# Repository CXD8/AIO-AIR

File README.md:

# AIO-AIR
 \
**Project Overview**\
This is a compact, custom air quality monitor built around the ESP32-S3. I designed it to be an all-in-one solution for tracking environmental data, giving me a much better understanding of the air quality in my workspace.\
## Disclaimer
- **This project is intended for educational and research purposes only**
- **The author accepts no liability for regulatory non-compliance resulting from use of this project**
- **Users are solely responsible for ensuring compliance with all applicable local laws and regulations**
This project is provided **as-is, with absolutely no warranty of any kind**, express or implied. The author(s) accept **zero responsibility or liability** for any outcome resulting from the use, assembly, or operation of this hardware - including but not limited to property damage, fire, personal injury, or death.

**Use entirely at your own risk. The author(s) have no responsibility whatsoever for anything that goes wrong.**
- **Regulatory Disclaimer**
This project may use uncertified radio frequency (RF) modules. These components may have not been independently tested or certified for compliance such as for FCC (USA), CE (EU), or any other regulatory framework.
ard.**. The author(s) accept no responsibility for any damage, injury, or death caused.
- **No certification.** This design has not been tested, certified, or approved for any commercial, consumer, safety-critical, or regulatory-controlled application.
- **No guarantees.** The author(s) make no guarantees regarding the accuracy or fitness for purpose of the schematic, BOM, firmware, or any associated documentation.
**By using, building, or operating this project in any form, you accept full and sole responsibility for all risks and any consequences that arise.**
By using this project in any form, you agree to assume all associated risks and responsibilities.

**How to Use**\
Flashing: No integrated usb flashing feature. You can use your choice of usb flashing device eg FT or CH chipsets, connect them respectively on the PCB via the headers. Copy firmware into Ardiuno IDE or preffered flashing software, then flash directly.\
Integration: The device is built to talk directly to Home Assistant via ESPHome/MQTT. Once you flash the firmware, it will show up as a sensor entity on your dashboard.\
Features: You can view real-time data on your dashboard or through the low power e ink display. Optional fan with control and speed, status etc. Flexible desing, connect any device to the respective power, uart or spi pins.\

**Why I Built This**\
Many makers do soldering, 3D printing, and working with various materials in an enclosed space.I designed this board to get accurate, reliable readings so I can actually manage the air quality while I work. Also for monitoring Co2 because sleep is important :) |
 \

Bill Of Materials
| **#** | **bom\.csv**                                             | ****  | ****  | ****        | ****                                         | ****  | ****                 | ****     | ****                | ****                              | ****                               | ****                       | ****        | ****              | ****                      | ****      | ****                                   | **** | **** | **** | ****         | ****          | ****           | ****                                                                                                                                                                        | ****           | ****                                                   |
|-------|----------------------------------------------------------|-------|-------|-------------|----------------------------------------------|-------|----------------------|----------|---------------------|-----------------------------------|------------------------------------|----------------------------|-------------|-------------------|---------------------------|-----------|----------------------------------------|------|------|------|--------------|---------------|----------------|-----------------------------------------------------------------------------------------------------------------------------------------------------------------------------|----------------|--------------------------------------------------------|
| 1     |                                                          |       |       |             |                                              |       |                      |          |                     |                                   | BOM Date Created:23/05/26          |                            |             |                   | BOM Export Date: 23/05/26 |           |                                        |      |      |      |              |               |                |                                                                                                                                                                             |                |                                                        |
| 2     |                                                          |       |       |             |                                              |       |                      |          |                     |                                   | EST LCSC TOTAL: $30\.73           |                            |             |                   |                           |           |                                        |      |      |      |              |               |                |                                                                                                                                                                             |                |                                                        |
| 3     |                                                       |       |       |             |                                              |       |                      |          |                     |                                   | TOTAL – 1 SEN55 Sensor: $92\.61           |                            |             |                   |                           |           |                                        |      |      |      |              |               |                |                                                                                                                                                                             |                |                                                        |
| 4     | Uploaded data                                            |       |       |             |                                              |       |                      |          |                     |                                   | LCSC Matching Results              |                            |             |                   |                           |           |                                        |      |      |      |              |               |                |                                                                                                                                                                             |                |                                                        |
| 5     | LCSC\#                                                   | Mfr\. | Mrf\# | Description | Package                                      | Value | Customer Part Number | Quantity | Target Price\(USD\) | Target Lead Time\(Business Days\) | Mrf\#                              | Mfr\.                      | Order Qty\. | Unit Price\(USD\) | Ext\.Price\(USD\)         | LCSC\#    | Package                                | Min  | Mult | SPQ  | Availability | Stock Status  | Customer Notes | Description                                                                                                                                                                 | Matched status | Product Link                                           |
| 6     | C15849                                                   |       |       |             | C0603                                        |       | \-                   | 11       |                     |                                   | CL10A105KB8NNNC                    | Samsung Electro\-Mechanics | 50          | 0\.0077           | 0\.39                     | C15849    | 0603                                   | 50   | 50   | 4000 | 4032550      | In Stock      |                | 1uF ±10% 50V Ceramic Capacitor X5R 0603                                                                                                                                     | Exact Matches  | https://www\.lcsc\.com/product\-detail/C15849\.html    |
| 7     | C96446                                                   |       |       |             | C0603                                        |       | \-                   | 10       |                     |                                   | CL10A106MA8NRNC                    | Samsung Electro\-Mechanics | 20          | 0\.0223           | 0\.45                     | C96446    | 0603                                   | 20   | 20   | 4000 | 277300       | In Stock      |                | 10uF ±20% 25V Ceramic Capacitor X5R 0603                                                                                                                                    | Exact Matches  | https://www\.lcsc\.com/product\-detail/C96446\.html    |
| 8     | C1591                                                    |       |       |             | C0603                                        |       | \-                   | 10       |                     |                                   | CL10B104KB8NNNC                    | Samsung Electro\-Mechanics | 100         | 0\.0032           | 0\.32                     | C1591     | 0603                                   | 100  | 100  | 4000 | 1456500      | In Stock      |                | 100nF ±10% 50V Ceramic Capacitor X7R 0603                                                                                                                                   | Exact Matches  | https://www\.lcsc\.com/product\-detail/C1591\.html     |
| 9     | C307467                                                  |       |       |             | C0603                                        |       | \-                   | 4        |                     |                                   | CL10A475KL8NRNC                    | Samsung Electro\-Mechanics | 5           | 0\.0304           | 0\.15                     | C307467   | 0603                                   | 5    | 5    | 4000 | 192075       | In Stock      |                | 4\.7uF ±10% 35V Ceramic Capacitor X5R 0603                                                                                                                                  | Exact Matches  | https://www\.lcsc\.com/product\-detail/C307467\.html   |
| 10    | C883598                                                  |       |       |             | C1206                                        |       | \-                   | 4        |                     |                                   | GRM31CR61A107MEA8L                 | muRata                     | 5           | 0\.1955           | 0\.98                     | C883598   | 1206                                   | 5    | 5    | 2000 | 209960       | In Stock      |                | 100uF ±20% 10V Ceramic Capacitor X5R 1206                                                                                                                                   | Exact Matches  | https://www\.lcsc\.com/product\-detail/C883598\.html   |
| 11    | C21122                                                   |       |       |             | C0603                                        |       | \-                   | 3        |                     |                                   | CL10B223KB8NNNC                    | Samsung Electro\-Mechanics | 50          | 0\.0046           | 0\.23                     | C21122    | 0603                                   | 50   | 50   | 4000 | 1335100      | In Stock      |                | 22nF ±10% 50V Ceramic Capacitor X7R 0603                                                                                                                                    | Exact Matches  | https://www\.lcsc\.com/product\-detail/C21122\.html    |
| 12    | C307467                                                  |       |       |             | C0603                                        |       | \-                   | 3        |                     |                                   | CL10A475KL8NRNC                    | Samsung Electro\-Mechanics | 5           | 0\.0304           | 0\.15                     | C307467   | 0603                                   | 5    | 5    | 4000 | 192075       | In Stock      |                | 4\.7uF ±10% 35V Ceramic Capacitor X5R 0603                                                                                                                                  | Exact Matches  | https://www\.lcsc\.com/product\-detail/C307467\.html   |
| 13    | C6119851                                                 |       |       |             | C0603                                        |       | \-                   | 2        |                     |                                   | CGA0603X5R475K350JT                | HRE                        | 20          | 0\.0304           | 0\.61                     | C6119851  | 0603                                   | 20   | 20   | 4000 | 18100        | In Stock      |                | 4\.7uF ±10% 35V Ceramic Capacitor X5R 0603                                                                                                                                  | Exact Matches  | https://www\.lcsc\.com/product\-detail/C6119851\.html  |
| 14    | C1591                                                    |       |       |             | C0603                                        |       | \-                   | 2        |                     |                                   | CL10B104KB8NNNC                    | Samsung Electro\-Mechanics | 100         | 0\.0032           | 0\.32                     | C1591     | 0603                                   | 100  | 100  | 4000 | 1456500      | In Stock      |                | 100nF ±10% 50V Ceramic Capacitor X7R 0603                                                                                                                                   | Exact Matches  | https://www\.lcsc\.com/product\-detail/C1591\.html     |
| 15    | C6563232                                                 |       |       |             | C0603                                        |       | \-                   | 1        |                     |                                   | 0603B112K500NT                     | FH                         | 100         | 0\.0030           | 0\.30                     | C6563232  | 0603                                   | 100  | 100  | 4000 | 400          | In Stock      |                | 1\.1nF ±10% 50V Ceramic Capacitor X7R 0603                                                                                                                                  | Exact Matches  | https://www\.lcsc\.com/product\-detail/C6563232\.html  |
| 16    | C1591                                                    |       |       |             | C0603                                        |       | \-                   | 1        |                     |                                   | CL10B104KB8NNNC                    | Samsung Electro\-Mechanics | 100         | 0\.0032           | 0\.32                     | C1591     | 0603                                   | 100  | 100  | 4000 | 1456500      | In Stock      |                | 100nF ±10% 50V Ceramic Capacitor X7R 0603                                                                                                                                   | Exact Matches  | https://www\.lcsc\.com/product\-detail/C1591\.html     |
| 17    | C86295                                                   |       |       |             | C0603                                        |       | \-                   | 1        |                     |                                   | CL10A226MP8NUNE                    | Samsung Electro\-Mechanics | 10          | 0\.0157           | 0\.16                     | C86295    | 0603                                   | 10   | 10   | 3000 | 1989760      | In Stock      |                | 22uF ±20% 10V Ceramic Capacitor X5R 0603                                                                                                                                    | Exact Matches  | https://www\.lcsc\.com/product\-detail/C86295\.html    |
| 18    | C98220                                                   |       |       |             | R0603                                        |       | \-                   | 5        |                     |                                   | RC0603FR\-0710KL                   | YAGEO                      | 100         | 0\.0015           | 0\.15                     | C98220    | 0603                                   | 100  | 100  | 5000 | 0            | Backordered   |                | 100mW 10k? 75V Thick Film Resistor ±100ppm/? ±1% 0603 Chip Resistor \- Surface Mount RoHS                                                                                   | Exact Matches  | https://www\.lcsc\.com/product\-detail/C98220\.html    |
| 19    | C14675                                                   |       |       |             | R0603                                        |       | \-                   | 5        |                     |                                   | RC0603FR\-07100KL                  | YAGEO                      | 100         | 0\.0014           | 0\.14                     | C14675    | 0603                                   | 100  | 100  | 5000 | 1073900      | In Stock      |                | 100mW 100k? 75V Thick Film Resistor ±100ppm/? ±1% 0603 Chip Resistor \- Surface Mount RoHS                                                                                  | Exact Matches  | https://www\.lcsc\.com/product\-detail/C14675\.html    |
| 20    | C25804                                                   |       |       |             | R0603                                        |       | \-                   | 4        |                     |                                   | 0603WAF1002T5E                     | UNI\-ROYAL                 | 100         | 0\.0014           | 0\.14                     | C25804    | 0603                                   | 100  | 100  | 5000 | 0            | Backordered   |                | 10k? ±1% 100mW 0603 Thick Film Resistor                                                                                                                                     | Exact Matches  | https://www\.lcsc\.com/product\-detail/C25804\.html    |
| 21    | C95177                                                   |       |       |             | R0603                                        |       | \-                   | 4        |                     |                                   | RC0603JR\-070RL                    | YAGEO                      | 100         | 0\.0014           | 0\.14                     | C95177    | 0603                                   | 100  | 100  | 5000 | 1026800      | In Stock      |                | 100mW 0? 75V Thick Film Resistor ±5% 0603 Chip Resistor \- Surface Mount RoHS                                                                                               | Exact Matches  | https://www\.lcsc\.com/product\-detail/C95177\.html    |
| 22    | C25804                                                   |       |       |             | R0603                                        |       | \-                   | 2        |                     |                                   | 0603WAF1002T5E                     | UNI\-ROYAL                 | 100         | 0\.0014           | 0\.14                     | C25804    | 0603                                   | 100  | 100  | 5000 | 0            | Backordered   |                | 10k? ±1% 100mW 0603 Thick Film Resistor                                                                                                                                     | Exact Matches  | https://www\.lcsc\.com/product\-detail/C25804\.html    |
| 23    | C114659                                                  |       |       |             | R0603                                        |       | \-                   | 2        |                     |                                   | RC0603FR\-0712KL                   | YAGEO                      | 100         | 0\.0016           | 0\.16                     | C114659   | 0603                                   | 100  | 100  | 5000 | 1073600      | In Stock      |                | 12k? 100mW 75V Thick Film Resistor ±100ppm/? ±1% 0603 Chip Resistor \- Surface Mount RoHS                                                                                   | Exact Matches  | https://www\.lcsc\.com/product\-detail/C114659\.html   |
| 24    | C52069115                                                |       |       |             | R0603                                        |       | \-                   | 1        |                     |                                   | MFCR0603F3R00Q9R                   | RESI                       | 5           | 0\.0840           | 0\.42                     | C52069115 | 0603                                   | 5    | 5    | 5000 | 4610         | In Stock      |                | 3? 400mW ±50ppm/? ±1% 0603 Chip Resistor \- Surface Mount RoHS                                                                                                              | Exact Matches  | https://www\.lcsc\.com/product\-detail/C52069115\.html |
| 25    | C23411                                                   |       |       |             | R0603                                        |       | \-                   | 1        |                     |                                   | 0603WAF470LT5E                     | UNI\-ROYAL                 | 100         | 0\.0051           | 0\.51                     | C23411    | 0603                                   | 100  | 100  | 5000 | 59400        | In Stock      |                | 470m? ±1% 100mW 0603 Thick Film Resistor                                                                                                                                    | Exact Matches  | https://www\.lcsc\.com/product\-detail/C23411\.html    |
| 26    | C22883                                                   |       |       |             | R0603                                        |       | \-                   | 1        |                     |                                   | 0603WAF1583T5E                     | UNI\-ROYAL                 | 100         | 0\.0014           | 0\.14                     | C22883    | 0603                                   | 100  | 100  | 5000 | 166400       | In Stock      |                | 158k? ±1% 100mW 0603 Thick Film Resistor                                                                                                                                    | Exact Matches  | https://www\.lcsc\.com/product\-detail/C22883\.html    |
| 27    | C107231                                                  |       |       |             | R0603                                        |       | \-                   | 1        |                     |                                   | RC0603FR\-0751KL                   | YAGEO                      | 100         | 0\.0016           | 0\.16                     | C107231   | 0603                                   | 100  | 100  | 5000 | 140700       | In Stock      |                | 100mW 51k? 75V Thick Film Resistor ±100ppm/? ±1% 0603 Chip Resistor \- Surface Mount RoHS                                                                                   | Exact Matches  | https://www\.lcsc\.com/product\-detail/C107231\.html   |
| 28    | C22892                                                   |       |       |             | R0603                                        |       | \-                   | 1        |                     |                                   | 0603WAF1822T5E                     | UNI\-ROYAL                 | 100         | 0\.0012           | 0\.12                     | C22892    | 0603                                   | 100  | 100  | 5000 | 17100        | In Stock      |                | 18\.2k? ±1% 100mW 0603 Thick Film Resistor                                                                                                                                  | Exact Matches  | https://www\.lcsc\.com/product\-detail/C22892\.html    |
| 29    | C105574                                                  |       |       |             | R0603                                        |       | \-                   | 1        |                     |                                   | RC0603FR\-07200KL                  | YAGEO                      | 100         | 0\.0016           | 0\.16                     | C105574   | 0603                                   | 100  | 100  | 5000 | 196200       | In Stock      |                | 100mW 200k? 75V Thick Film Resistor ±100ppm/? ±1% 0603 Chip Resistor \- Surface Mount RoHS                                                                                  | Exact Matches  | https://www\.lcsc\.com/product\-detail/C105574\.html   |
| 30    | C2930091                                                 |       |       |             | R0603                                        |       | \-                   | 1        |                     |                                   | FRC0603F3003TS                     | FOJAN                      | 100         | 0\.0011           | 0\.11                     | C2930091  | 0603                                   | 100  | 100  | 5000 | 1794600      | In Stock      |                | 300k? ±1% 100mW 0603 Thick Film Resistor                                                                                                                                    | Exact Matches  | https://www\.lcsc\.com/product\-detail/C2930091\.html  |
| 31    | C105579                                                  |       |       |             | R0603                                        |       | \-                   | 1        |                     |                                   | RC0603FR\-0747KL                   | YAGEO                      | 100         | 0\.0016           | 0\.16                     | C105579   | 0603                                   | 100  | 100  | 5000 | 370600       | In Stock      |                | 100mW 47k? 75V Thick Film Resistor ±100ppm/? ±1% 0603 Chip Resistor \- Surface Mount RoHS                                                                                   | Exact Matches  | https://www\.lcsc\.com/product\-detail/C105579\.html   |
| 32    | C2998085                                                 |       |       |             | R0603                                        |       | \-                   | 1        |                     |                                   | FRC0603F9001TS                     | FOJAN                      | 0           | \-                | \-                        | C2998085  | 0603                                   | 100  | 100  | 5000 | 0            | discountinued |                | 9k? ±1% 100mW 0603 Thick Film Resistor                                                                                                                                      | Exact Matches  | https://www\.lcsc\.com/product\-detail/C2998085\.html  |
| 33    | C109318                                                  |       |       |             | R0603                                        |       | \-                   | 1        |                     |                                   | RC0603FR\-0710RL                   | YAGEO                      | 100         | 0\.0039           | 0\.39                     | C109318   | 0603                                   | 100  | 100  | 5000 | 3822900      | In Stock      |                | 100mW 10? 75V Thick Film Resistor ±1% ±200ppm/? 0603 Chip Resistor \- Surface Mount RoHS                                                                                    | Exact Matches  | https://www\.lcsc\.com/product\-detail/C109318\.html   |
| 34    | C22461457                                                |       |       |             | RES\-ADJ\-SMD\_3P\-L3\.8\-W3\.7\_VGF39NCHXT  |       | \-                   | 1        |                     |                                   | VGF39NCHXT\-B201                   | HDK                        | 5           | 0\.1107           | 0\.55                     | C22461457 | SMD\-3P,3\.8x3\.7mm                    | 5    | 5    | 2500 | 2525         | In Stock      |                | 200? ±25% 150mW SMD Potentiometers, Variable Resistors                                                                                                                      | Exact Matches  | https://www\.lcsc\.com/product\-detail/C22461457\.html |
| 35    | C105881                                                  |       |       |             | R0603                                        |       | \-                   | 1        |                     |                                   | RC0603FR\-07330RL                  | YAGEO                      | 100         | 0\.0015           | 0\.15                     | C105881   | 0603                                   | 100  | 100  | 5000 | 351200       | In Stock      |                | 100mW 330? 75V Thick Film Resistor ±100ppm/? ±1% 0603 Chip Resistor \- Surface Mount RoHS                                                                                   | Exact Matches  | https://www\.lcsc\.com/product\-detail/C105881\.html   |
| 36    | C2875591                                                 |       |       |             | IND\-SMD\_L4\.7\-W4\.7                       |       | \-                   | 2        |                     |                                   | CDH4D28N\-100M                     | MINGSTAR                   | 5           | 0\.1803           | 0\.90                     | C2875591  | SMD,4\.7x4\.7mm                        | 5    | 5    | 2500 | 2505         | In Stock      |                | 1A 10uH ±20% 128\.3m? SMD,4\.7x4\.7mm Fixed Inductors RoHS                                                                                                                  | Exact Matches  | https://www\.lcsc\.com/product\-detail/C2875591\.html  |
| 37    | C436534                                                  |       |       |             | IND\-SMD\_L5\.4\-W5\.2\_PSPMAA0503           |       | \-                   | 1        |                     |                                   | PSPMAA0503\-3R3M\-ANP              | PROD Tech                  | 5           | 0\.1292           | 0\.65                     | C436534   | SMD,5\.4x5\.2mm                        | 5    | 5    | 2000 | 4805         | In Stock      |                | 5A 3\.3uH ±20% 6A 38m? SMD,5\.4x5\.2mm Fixed Inductors RoHS                                                                                                                 | Exact Matches  | https://www\.lcsc\.com/product\-detail/C436534\.html   |
| 38    | C7436545                                                 |       |       |             | SOD\-123\_L2\.8\-W1\.8\-LS3\.9\-FD           |       | \-                   | 4        |                     |                                   | MBR0530T1G                         | FUXINSEMI                  | 10          | 0\.0162           | 0\.16                     | C7436545  | SOD\-123                               | 10   | 10   | 3000 | 5700         | In Stock      |                | Diode Independent 30V 0\.5A Surface Mount SOD\-123                                                                                                                          | Exact Matches  | https://www\.lcsc\.com/product\-detail/C7436545\.html  |
| 39    | C110921                                                  |       |       |             | SOD\-123F\_L2\.8\-W1\.8\-LS3\.7\-RD          |       | \-                   | 1        |                     |                                   | PMEG2010AEH,115                    | Nexperia                   | 5           | 0\.2158           | 1\.08                     | C110921   | SOD\-123F                              | 5    | 5    | 3000 | 5360         | In Stock      |                | Diode 1 Independent 20V 1A Surface Mount SOD\-123F                                                                                                                          | Exact Matches  | https://www\.lcsc\.com/product\-detail/C110921\.html   |
| 40    | C150716                                                  |       |       |             | SOT\-223\_L6\.7\-W3\.5\-P2\.30\-BR           |       | \-                   | 3        |                     |                                   | AP2114H\-3\.3TRG1                  | DIODES                     | 5           | 0\.1763           | 0\.88                     | C150716   | SOT\-223                               | 5    | 5    | 4000 | 14765        | In Stock      |                | 3\.3V Positive Fixed SOT\-223 Voltage Regulators \- Linear, Low Drop Out \(LDO\) Regulators RoHS                                                                            | Exact Matches  | https://www\.lcsc\.com/product\-detail/C150716\.html   |
| 41    | C15651                                                   |       |       |             | SOT\-23\-5\_L3\.0\-W1\.7\-P0\.95\-LS2\.8\-BL |       | \-                   | 3        |                     |                                   | RT9193\-33GB                       | RICHTEK                    | 5           | 0\.1271           | 0\.64                     | C15651    | SOT\-23\-5                             | 5    | 5    | 3000 | 0            | Backordered   |                | 3\.3V Positive Fixed SOT\-23\-5 Voltage Regulators \- Linear, Low Drop Out \(LDO\) Regulators RoHS                                                                          | Exact Matches  | https://www\.lcsc\.com/product\-detail/C15651\.html    |
| 42    | C3013946                                                 |       |       |             | WIRELM\-SMD\_ESP32\-S3\-WROOM\-1U            |       | \-                   | 1        |                     |                                   | ESP32\-S3\-WROOM\-1U\-N16R8        | ESPRESSIF                  | 1           | 5\.5217           | 5\.52                     | C3013946  | SMD,19\.2x18mm                         | 1    | 1    | 650  | 0            | Backordered   |                | 2\.4GHz ESP32\-S3R8 \-103\.5dBm SMD,19\.2x18mm RF Transceiver Modules and Modems RoHS                                                                                       | Exact Matches  | https://www\.lcsc\.com/product\-detail/C3013946\.html  |
| 43    | C113659                                                  |       |       |             | VSSOP\-8\_L3\.0\-W3\.0\-P0\.65\-LS5\.0\-BL   |       | \-                   | 1        |                     |                                   | TPS61085DGKR                       | TI                         | 1           | 0\.5915           | 0\.59                     | C113659   | VSSOP\-8\-0\.65mm                      | 1    | 1    | 2500 | 4530         | In Stock      |                | Boost Adjustable 2\.8V~18\.5V 2A 2\.3V~6V VSSOP\-8\-0\.65mm Voltage Regulators \- DC DC Switching Regulators RoHS                                                           | Exact Matches  | https://www\.lcsc\.com/product\-detail/C113659\.html   |
| 44    | C664389                                                  |       |       |             | SOT\-23\-5\_L3\.0\-W1\.6\-P0\.95\-LS2\.8\-BL |       | \-                   | 1        |                     |                                   | LT1615IS5\#TRPBF                   | ADI                        | 1           | 6\.0924           | 6\.09                     | C664389   | TSOT\-23\-5                            | 1    | 1    | 2500 | 143          | In Stock      |                | Boost Adjustable 1V~15V 1\.23V~34V 300mA TSOT\-23\-5 Voltage Regulators \- DC DC Switching Regulators RoHS                                                                  | Exact Matches  | https://www\.lcsc\.com/product\-detail/C664389\.html   |
| 45    | C3293144                                                 |       |       |             | SW\-SMD\_8P\-L6\.7\-W5\.4\-P1\.27\-LS8\.4    |       | \-                   | 1        |                     |                                   | DSHP04TSGER                        | kangshen                   | 4           | 0\.5202           | 2\.08                     | C3293144  | SMD,P=1\.27mm                          | 4    | 4    | 2000 | 29172        | In Stock      |                | Dip Switch SPST 4 Position Surface Mount\-8P,5\.4x6\.6mm 25mA 24V                                                                                                           | Exact Matches  | https://www\.lcsc\.com/product\-detail/C3293144\.html  |
| 46    | C963206                                                  |       |       |             | SW\-SMD\_MK\-12C02\-G020                     |       | \-                   | 2        |                     |                                   | MK\-12C02\-G020                    | G\-Switch                  | 5           | 0\.1168           | 0\.58                     | C963206   | SMD,6\.6x1\.4mm                        | 5    | 5    | 3000 | 9555         | In Stock      |                | Slide Switch SPDT 1A @ 6V Surface Mount, Right Angle Rectangular Columnar 6\.6mm                                                                                            | Exact Matches  | https://www\.lcsc\.com/product\-detail/C963206\.html   |
| 47    | C720477                                                  |       |       |             | SW\-SMD\_L3\.9\-W3\.0\-P4\.45                |       | \-                   | 2        |                     |                                   | TS\-1088\-AR02016                  | XUNPU                      | 10          | 0\.0538           | 0\.54                     | C720477   | SMD,4x3mm                              | 10   | 10   | 4000 | 582850       | In Stock      |                | Tactile Switch SPST 160gf 2mm SMD \(SMT\) Tab 4mm x 3mm Surface Mount                                                                                                       | Exact Matches  | https://www\.lcsc\.com/product\-detail/C720477\.html   |
| 48    | C2856796                                                 |       |       |             | FPC\-SMD\_6P\-P0\.50\_XUNPU\_FPC\-05F\-6PH20 |       | \-                   | 3        |                     |                                   | FPC\-05F\-6PH20                    | XUNPU                      | 5           | 0\.1000           | 0\.50                     | C2856796  | SMD,P=0\.5mm,Surface Mount,Right Angle | 5    | 5    | 2000 | 66135        | In Stock      |                | FFC/FPC Connector 6 Position 0\.5mm Pitch Bottom Contact Surface Mount, Right Angle \-25?~\+85?                                                                             | Exact Matches  | https://www\.lcsc\.com/product\-detail/C2856796\.html  |
| 49    | C240840                                                  |       |       |             | 4PIN\_FAN\_PWM                               |       | \-                   | 1        |                     |                                   | 470531000                          | MOLEX                      | 5           | 0\.1803           | 0\.90                     | C240840   | Through Hole,P=2\.54mm                 | 5    | 5    | 1000 | 21670        | In Stock      |                | Connector Header 4 position 2\.54mm Pitch Through Hole                                                                                                                      | Exact Matches  | https://www\.lcsc\.com/product\-detail/C240840\.html   |
| 50    |                                                          |       |       |             | FLASH                                        |       | \-                   | 1        |                     |                                   | \-                                 | \-                         | \-          | \-                | \-                        | \-        | \-                                     | \-   | \-   | \-   | \-           | \-            |                | \-                                                                                                                                                                          | \-             |                                                        |
| 51    | C3446015                                                 |       |       |             | FPC\-SMD\_XUNPU\-FPC\-0\.5FX\-24PWBH20       |       | \-                   | 1        |                     |                                   | FPC\-0\.5FX\-24PWBH20              | XUNPU                      | 5           | 0\.1424           | 0\.71                     | C3446015  | SMD,P=0\.5mm                           | 5    | 5    | 2000 | 3065         | In Stock      |                | Hinged Lid \-25?~\+85? 24P 0\.5mm 500mA 50V Tin Bottom Contact Surface Mount, Right Angle Phosphor bronze SMD,P=0\.5mm FFC, FPC \(Flat Flexible\) Connector Assemblies RoHS | Exact Matches  | https://www\.lcsc\.com/product\-detail/C3446015\.html  |
| 52    | C219228                                                  |       |       |             | LED\-SMD\_L1\.6\-W0\.8\-RD\-WHITE\-2         |       | \-                   | 1        |                     |                                   | HL\-PST\-1608H233W\(8000\-12000K\) | HONGLITRONIC               | 20          | 0\.0197           | 0\.39                     | C219228   | 0603                                   | 20   | 20   | 4000 | 73360        | In Stock      |                | White LED Indication \- Discrete 3\.3V 0603                                                                                                                                 | Exact Matches  | https://www\.lcsc\.com/product\-detail/C219228\.html   |
| 53    | https://www\.aliexpress\.com/item/1005009258276115\.html |       |       |             | 4\.2”E\-INK                                  |       | \-                   | 1        |                     |                                   | GDEY042T81\-T02                    | GooDisplay                 | 1           | 22\.46            | 22\.46                    | \-        | \-                                     | \-   | \-   | \-   | \-           | \-            |                | \-                                                                                                                                                                          | ALIEXPRESS     |                                                        |
| 54    | C3289597                                                 |       |       |             | SOT\-323\_L2\.0\-W1\.3\-P1\.30\-LS2\.1\-BR   |       | \-                   | 1        |                     |                                   | SI1308EDL\-T1\-BE3                 | VISHAY                     | 1           | 0\.4041           | 0\.40                     | C3289597  | SC\-70\-3                              | 1    | 1    | 3000 | 2243         | In Stock      |                | N\-Channel 30V 1\.5A 0\.5W Surface Mount SC\-70\-3                                                                                                                          | Exact Matches  | https://www\.lcsc\.com/product\-detail/C3289597\.html  |
| 55    | https://www\.aliexpress\.com/item/1005008474655738\.html |       |       |             | 24 PIN FPC CABLE                             |       | \-                   | 1        |                     |                                   | \-                                 | \-                         | \-          | 0\.99             | 0\.99                     | \-        | \-                                     | \-   | \-   | \-   | \-           | \-            |                | \-                                                                                                                                                                          | ALIEXPRESS     |                                                        |
| 56    | https://www\.aliexpress\.com/item/1005006672233038\.html |       | \-    |             | SEN55                                        | \-    | \-                   | 1        | \-                  | \-                                | SEN55                              | Sensirion                  |             | 38\.43            | 38\.43                    | \-        | \-                                     | \-   | \-   | \-   | \-           | \-            |                | \-                                                                                                                                                                          | ALIEXPRESS     |                                                        |

Changelog\
06/30/2026
New Housing/Case. Improved viewing angles, fits larger sensors, looks much better.
03/31/2026
Optimise PCB size under 100mmx100mm for cheaper fabrication costs.

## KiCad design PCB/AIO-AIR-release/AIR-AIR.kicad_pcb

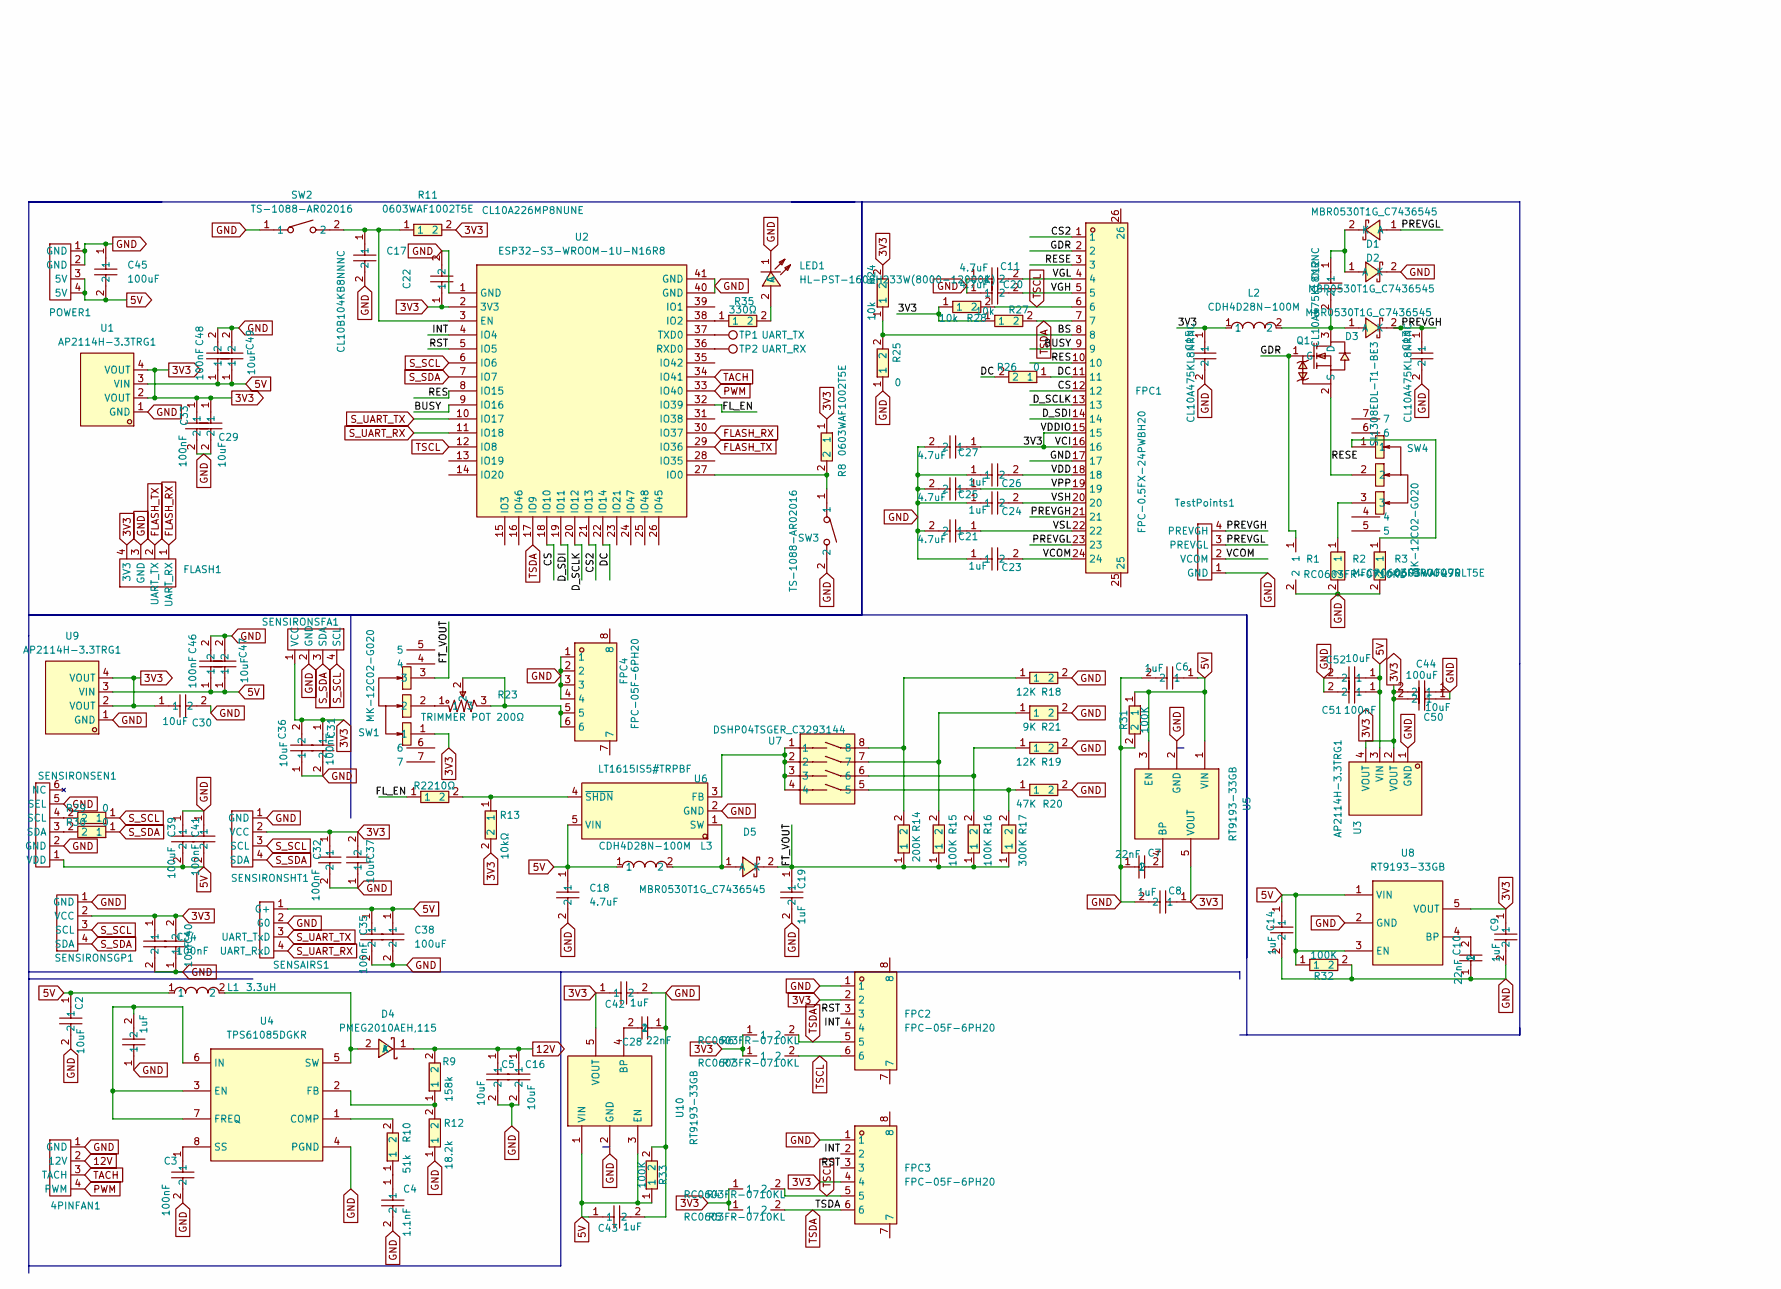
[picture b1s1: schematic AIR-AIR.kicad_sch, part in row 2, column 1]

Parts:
4PINFAN1: 4PIN_FAN_PWM
C1, C6, C8, C9, C14, C19, C23, C24, C26, C42, C43: 1uF; C0603; LCSC Part C15849
C2, C5, C16, C30, C36, C37, C40, C47, C49, C52: 10uF; C0603; LCSC Part C96446
C3, C31, C32, C33, C34, C35, C41, C46, C48, C51: 100nF; C0603; LCSC Part C1591
C4: 1.1nF; C0603; LCSC Part C6563232
C7, C10, C28: 22nF; C0603; LCSC Part C21122
C11, C20: 4.7uF; C0603; LCSC Part C6119851
C12, C13, C15: CL10A475KL8NRNC; C0603; LCSC Part C307467
C17: CL10B104KB8NNNC; C0603; LCSC Part C1591
C18, C21, C25, C27: 4.7uF; C0603; LCSC Part C307467
C22: CL10A226MP8NUNE; C0603; LCSC Part C86295
C29, C50: 10uF; C0603; LCSC Part C1591
C38, C39, C44, C45: 100uF; C1206; LCSC Part C883598
D1, D2, D3, D5: MBR0530T1G_C7436545; SOD-123_L2.8-W1.8-LS3.9-FD; LCSC Part C7436545
D4: PMEG2010AEH,115; SOD-123F_L2.8-W1.8-LS3.7-RD; LCSC Part C110921
FLASH1: FLASH
FPC1: FPC-0.5FX-24PWBH20; FPC-SMD_XUNPU-FPC-0.5FX-24PWBH20; LCSC Part C3446015
FPC2, FPC3, FPC4: FPC-05F-6PH20; FPC-SMD_6P-P0.50_XUNPU_FPC-05F-6PH20; LCSC Part C2856796
L1: 3.3uH; IND-SMD_L5.4-W5.2_PSPMAA0503; LCSC Part C436534
L2, L3: CDH4D28N-100M; IND-SMD_L4.7-W4.7; LCSC Part C2875591
LED1: HL-PST-1608H233W(8000-12000K); LED-SMD_L1.6-W0.8-RD-WHITE-2; LCSC Part C219228
POWER1: POWER
Q1: SI1308EDL-T1-BE3; SOT-323_L2.0-W1.3-P1.30-LS2.1-BR; LCSC Part C3289597
R1, R4, R5, R6, R7: RC0603FR-0710KL; R0603; LCSC Part C98220
R2: MFCR0603F3R00Q9R; R0603; LCSC Part C52069115
R3: 0603WAF470LT5E; R0603; LCSC Part C23411
R8, R11: 0603WAF1002T5E; R0603; LCSC Part C25804
R9: 158k; R0603; LCSC Part C22883
R10: 51k; R0603; LCSC Part C107231
R12: 18.2k; R0603; LCSC Part C22892
R13: 10kΩ; R0603; LCSC Part C25804
R14: 200K; R0603; LCSC Part C105574
R15, R16, R31, R32, R33: 100K; R0603; LCSC Part C14675
R17: 300K; R0603; LCSC Part C2930091
R18, R19: 12K; R0603; LCSC Part C114659
R20: 47K; R0603; LCSC Part C105579
R21: 9K; R0603; LCSC Part C2998085
R22: 10Ω; R0603; LCSC Part C109318
R23: TRIMMER POT 200Ω; RES-ADJ-SMD_3P-L3.8-W3.7_VGF39NCHXT; LCSC Part C22461457
R24, R27, R28: 10k; R0603; LCSC Part C25804
R25, R26, R29, R30: 0; R0603; LCSC Part C95177
R35: 330Ω; R0603; LCSC Part C105881
SENSAIRS1: SENSAIR_S88
SENSIRONSEN1: SENSIRON_SEN55
SENSIRONSFA1: SENSIRON_SFA40
SENSIRONSGP1: SENSIRON_SGP41
SENSIRONSHT1: SENSIRON_SHT45
SW1, SW4: MK-12C02-G020; SW-SMD_MK-12C02-G020; LCSC Part C963206
SW2, SW3: TS-1088-AR02016; SW-SMD_L3.9-W3.0-P4.45; LCSC Part C720477
TP1: UART_TX
TP2: UART_RX
TestPoints1: TestPoints
U1, U3, U9: AP2114H-3.3TRG1; SOT-223_L6.7-W3.5-P2.30-BR; LCSC Part C150716
U2: ESP32-S3-WROOM-1U-N16R8; WIRELM-SMD_ESP32-S3-WROOM-1U; LCSC Part C3013946
U4: TPS61085DGKR; VSSOP-8_L3.0-W3.0-P0.65-LS5.0-BL; LCSC Part C113659
U5, U8, U10: RT9193-33GB; SOT-23-5_L3.0-W1.7-P0.95-LS2.8-BL; LCSC Part C15651
U6: LT1615IS5#TRPBF; SOT-23-5_L3.0-W1.6-P0.95-LS2.8-BL; LCSC Part C664389
U7: DSHP04TSGER_C3293144; SW-SMD_8P-L6.7-W5.4-P1.27-LS8.4; LCSC Part C3293144

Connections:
3V3: C8.1, C9.1, C15.1, C22.1, C27.1, C29.1, C30.1, C31.1, C32.1, C33.1, C34.1, C36.2, C37.2, C40.2, C42.1, C44.2, C50.2, FLASH1.4 (3V3), FPC1.15, FPC1.16, FPC2.2, FPC3.4, L2.1, R4.1, R5.1, R6.1, R7.1, R8.1, R11.2, R13.2, R24.2, R27.1, R28.1, SENSIRONSFA1.1 (VCC), SENSIRONSGP1.2 (VCC), SENSIRONSHT1.2 (VCC), SW1.1, U1.2 (VOUT), U1.4 (VOUT), U2.2 (3V3), U3.2 (VOUT), U3.4 (VOUT), U5.5 (VOUT), U8.5 (VOUT), U9.2 (VOUT), U9.4 (VOUT), U10.5 (VOUT)
5V: C2.1, C6.1, C14.1, C18.1, C35.1, C38.1, C39.2, C41.2, C43.1, C45.2, C46.1, C47.1, C48.1, C49.1, C51.1, C52.1, L1.1, L3.1, POWER1.3 (5V), POWER1.4 (5V), R31.1, R32.1, R33.1, SENSAIRS1.1 (G+), SENSIRONSEN1.1 (VDD), U1.3 (VIN), U3.3 (VIN), U5.1 (VIN), U5.3 (EN), U6.5 (VIN), U8.1 (VIN), U8.3 (EN), U9.3 (VIN), U10.1 (VIN), U10.3 (EN)
12V: 4PINFAN1.2 (12V), C5.1, C16.1, D4.1 (K), R9.2
/BS: FPC1.8, R24.1, R25.2
/BUSY: FPC1.9, U2.9 (IO16)
/CS: FPC1.12, U2.18 (IO10)
/CS2: FPC1.1, U2.21 (IO13)
/DC: FPC1.11, R26.1, R26.2, U2.22 (IO14)
/D_SCLK: FPC1.13, U2.20 (IO12)
/D_SDI: FPC1.14, U2.19 (IO11)
/FL_EN: R22.1, U2.32 (IO39)
/FT_VOUT: C19.1, D5.2 (K), R14.1, R15.1, R16.1, R17.1, SW1.3
/GDR: FPC1.2, Q1.1 (G), R1.1
/INT: FPC2.4, FPC3.2, U2.4 (IO4)
/PREVGH: C13.1, D3.2 (K), FPC1.21, TestPoints1.4 (PREVGH)
/PREVGL: D1.1 (A), FPC1.23, TestPoints1.3 (PREVGL)
/RES: FPC1.10, U2.8 (IO15)
/RESE: FPC1.3, Q1.2 (S), SW4.2
/RST: FPC2.3, FPC3.3, U2.5 (IO5)
/VCOM: C23.2, FPC1.24, TestPoints1.2 (VCOM)
/VDD: C26.2, FPC1.18
/VGH: C20.2, FPC1.5
/VGL: C11.2, FPC1.4
/VPP: C25.1, FPC1.19
/VSH: C24.2, FPC1.20
/VSL: C21.1, FPC1.22
FLASH_RX: FLASH1.1 (UART_RX), U2.30 (IO37)
FLASH_TX: FLASH1.2 (UART_TX), U2.29 (IO36)
GND: 4PINFAN1.1 (GND), C1.1, C2.2, C3.2, C4.2, C5.2, C6.2, C7.1, C8.2, C9.2, C10.1, C11.1, C13.2, C14.2, C15.2, C16.2, C17.2, C18.2, C19.2, C20.1, C21.2, C22.2, C23.1, C24.1, C25.2, C26.1, C27.2, C28.1, C29.2, C30.2, C31.2, C32.2, C33.2, C34.2, C35.2, C36.1, C37.1, C38.2, C39.1, C40.1, C41.1, C42.2, C43.2, C44.1, C45.1, C46.2, C47.2, C48.2, C49.2, C50.1, C51.2, C52.2, D2.2 (K), FLASH1.3 (GND), FPC1.17, FPC2.1, FPC3.1, FPC4.1, FPC4.2, FPC4.3, FPC4.4, LED1.1 (C), POWER1.1 (GND), POWER1.2 (GND), R1.2, R2.2, R3.2, R12.1, R18.2, R19.2, R20.2, R21.2, R25.1, R31.2, R32.2, R33.2, SENSAIRS1.2 (G0), SENSIRONSEN1.2 (GND), SENSIRONSEN1.5 (SEL), SENSIRONSFA1.2 (GND), SENSIRONSGP1.1 (GND), SENSIRONSHT1.1 (GND), SW2.1, SW3.2, TestPoints1.1 (GND), U1.1 (GND), U2.1 (GND), U2.40 (GND), U2.41 (GND), U3.1 (GND), U4.4 (PGND), U5.2 (GND), U6.2 (GND), U8.2 (GND), U9.1 (GND), U10.2 (GND)
unnamed: C4.1, R10.1
unnamed: C12.1, D1.2 (K), D2.1 (A)
unnamed: C12.2, D3.1 (A), L2.2, Q1.3 (D)
unnamed: D4.2 (A), L1.2, U4.5 (SW)
unnamed: D5.1 (A), L3.2, U6.1 (SW)
unnamed: FPC4.5, FPC4.6, R23.2, R23.3
unnamed: LED1.2 (A), R35.2
unnamed: R2.1, SW4.3
unnamed: R3.1, SW4.1
unnamed: R14.2, R18.1, U7.8
unnamed: R15.2, R21.1, U7.7
unnamed: R16.2, R19.1, U7.6
unnamed: R17.2, R20.1, U7.5
unnamed: R23.1, SW1.2
unnamed: R29.2, SENSIRONSEN1.4 (SCL)
unnamed: R30.2, SENSIRONSEN1.3 (SDA)
unnamed: C17.1, R11.1, SW2.2, U2.3 (EN)
unnamed: R8.2, SW3.1, U2.27 (IO0)
unnamed: R35.1, U2.38 (IO2)
unnamed: TP2.1, U2.36 (RXD0)
unnamed: TP1.1, U2.37 (TXD0)
unnamed: R10.2, U4.1 (COMP)
unnamed: C1.2, U4.3 (EN), U4.6 (IN), U4.7 (FREQ)
unnamed: R9.1, R12.2, U4.2 (FB)
unnamed: C3.1, U4.8 (SS)
unnamed: C7.2, U5.4 (BP)
unnamed: U6.3 (FB), U7.1, U7.2, U7.3, U7.4
unnamed: R13.1, R22.2, U6.4 (~SHDN)
unnamed: C10.2, U8.4 (BP)
unnamed: C28.2, U10.4 (BP)
PWM: 4PINFAN1.4 (PWM), U2.33 (IO40)
S_SCL: R29.1, SENSIRONSFA1.4 (SCL), SENSIRONSGP1.3 (SCL), SENSIRONSHT1.3 (SCL), U2.6 (IO6)
S_SDA: R30.1, SENSIRONSFA1.3 (SDA), SENSIRONSGP1.4 (SDA), SENSIRONSHT1.4 (SDA), U2.7 (IO7)
S_UART_RX: SENSAIRS1.4 (UART_RxD), U2.11 (IO18)
S_UART_TX: SENSAIRS1.3 (UART_TxD), U2.10 (IO17)
TACH: 4PINFAN1.3 (TACH), U2.34 (IO41)
TSCL: FPC1.6, FPC2.6, FPC3.5, R4.2, R7.2, R28.2, U2.12 (IO8)
TSDA: FPC1.7, FPC2.5, FPC3.6, R5.2, R6.2, R27.2, U2.17 (IO9)

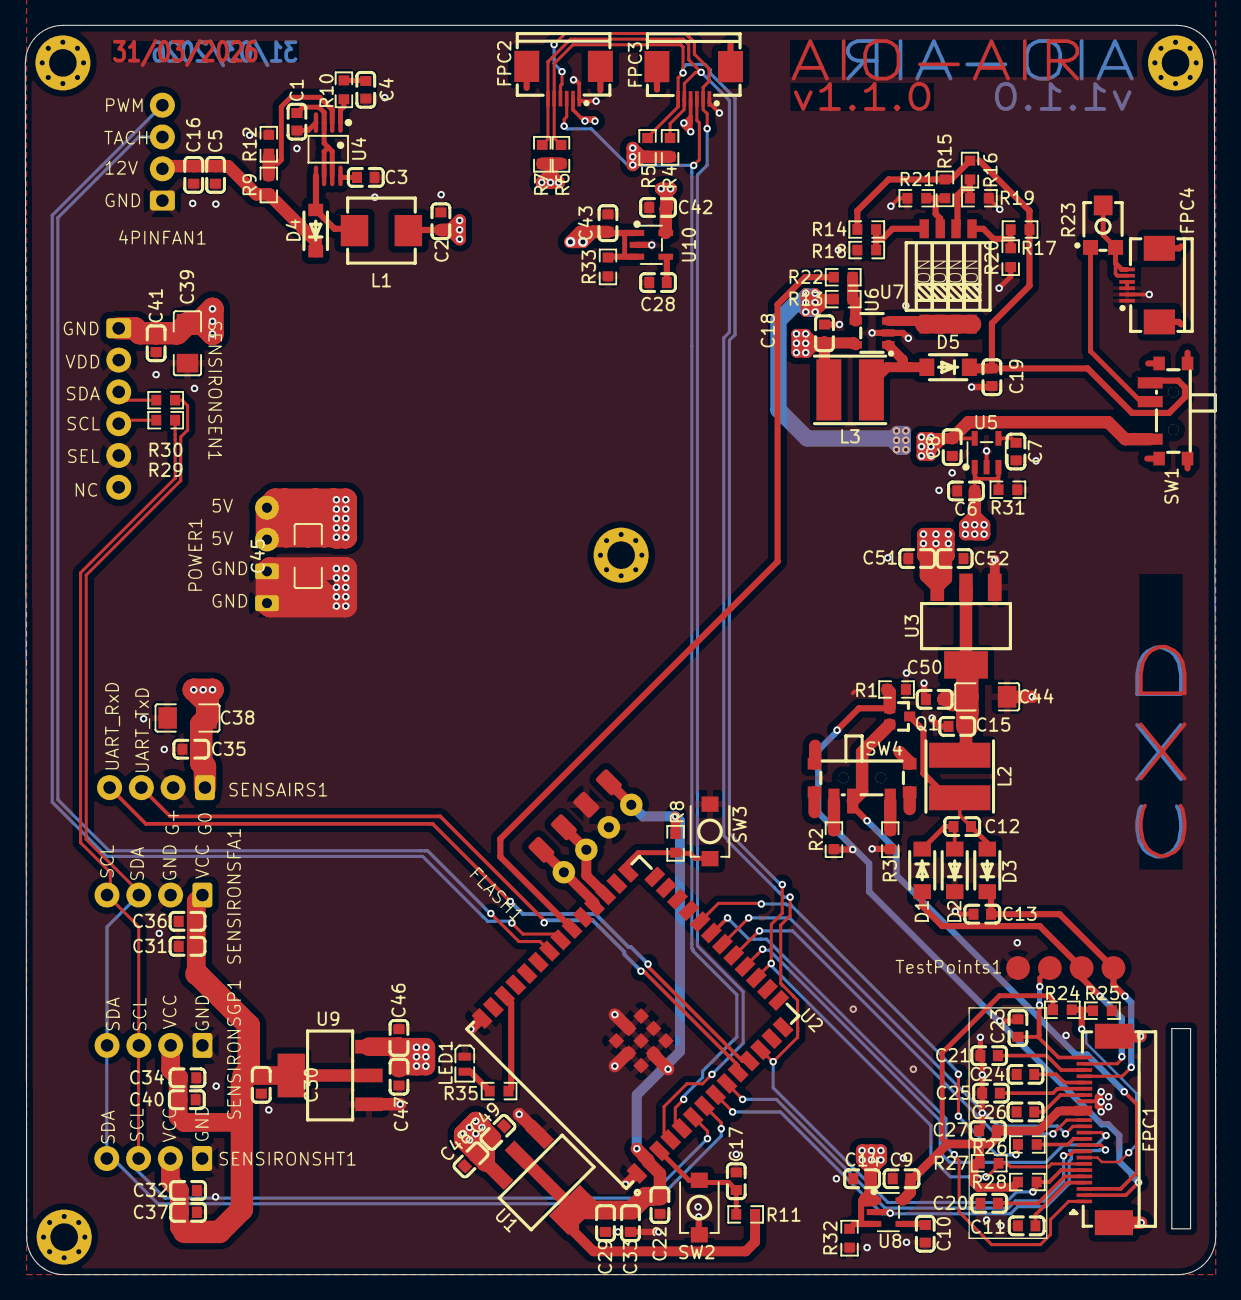
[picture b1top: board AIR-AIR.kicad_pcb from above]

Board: 4 copper layers, 95.1 x 99.8 mm, 123 parts (0 on the bottom side), 65 nets.

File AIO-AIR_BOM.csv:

Index,Designators,Part_Value,Package,LCSC_Part_Number,Quantity
1,"C1, C6, C8, C9, C14, C19, C23, C24, C26, C42, C43",1uF,C0603,C15849,11
2,"C2, C5, C16, C30, C36, C37, C40, C47, C49, C52",10uF,C0603,C96446,10
3,"C3, C31, C32, C33, C34, C35, C41, C46, C48, C51",100nF,C0603,C1591,10
4,"C18, C21, C25, C27",4.7uF,C0603,C307467,4
5,"C38, C39, C44, C45",100uF,C1206,C883598,4
6,"C7, C10, C28",22nF,C0603,C21122,3
7,"C12, C13, C15",CL10A475KL8NRNC,C0603,C307467,3
8,"C11, C20",4.7uF,C0603,C6119851,2
9,"C29, C50",10uF,C0603,C1591,2
10,C4,1.1nF,C0603,C6563232,1
11,C17,CL10B104KB8NNNC,C0603,C1591,1
12,C22,CL10A226MP8NUNE,C0603,C86295,1
13,"R1, R4, R5, R6, R7",RC0603FR-0710KL,R0603,C98220,5
14,"R15, R16, R31, R32, R33",100K,R0603,C14675,5
15,"R13, R24, R27, R28",10k,R0603,C25804,4
16,"R25, R26, R29, R30",0,R0603,C95177,4
17,"R8, R11",0603WAF1002T5E,R0603,C25804,2
18,"R18, R19",12K,R0603,C114659,2
19,R2,MFCR0603F3R00Q9R,R0603,C52069115,1
20,R3,0603WAF470LT5E,R0603,C23411,1
21,R9,158k,R0603,C22883,1
22,R10,51k,R0603,C107231,1
23,R12,18.2k,R0603,C22892,1
24,R14,200K,R0603,C105574,1
25,R17,300K,R0603,C2930091,1
26,R20,47K,R0603,C105579,1
27,R21,9K,R0603,C2998085,1
28,R22,10Ω,R0603,C109318,1
29,R23,"TRIMMER POT 200Ω",RES-ADJ-SMD_3P-L3.8-W3.7_VGF39NCHXT,C22461457,1
30,R35,330Ω,R0603,C105881,1
31,"L2, L3",CDH4D28N-100M,IND-SMD_L4.7-W4.7,C2875591,2
32,L1,3.3uH,IND-SMD_L5.4-W5.2_PSPMAA0503,C436534,1
33,"D1, D2, D3, D5",MBR0530T1G_C7436545,SOD-123_L2.8-W1.8-LS3.9-FD,C7436545,4
34,D4,"PMEG2010AEH,115",SOD-123F_L2.8-W1.8-LS3.7-RD,C110921,1
35,"U1, U3, U9",AP2114H-3.3TRG1,SOT-223_L6.7-W3.5-P2.30-BR,C150716,3
36,"U5, U8, U10",RT9193-33GB,SOT-23-5_L3.0-W1.7-P0.95-LS2.8-BL,C15651,3
37,U2,ESP32-S3-WROOM-1U-N16R8,WIRELM-SMD_ESP32-S3-WROOM-1U,C3013946,1
38,U4,TPS61085DGKR,VSSOP-8_L3.0-W3.0-P0.65-LS5.0-BL,C113659,1
39,U6,LT1615IS5#TRPBF,SOT-23-5_L3.0-W1.6-P0.95-LS2.8-BL,C664389,1
40,U7,DSHP04TSGER_C3293144,SW-SMD_8P-L6.7-W5.4-P1.27-LS8.4,C3293144,1
41,"SW1, SW4",MK-12C02-G020,SW-SMD_MK-12C02-G020,C963206,2
42,"SW2, SW3",TS-1088-AR02016,SW-SMD_L3.9-W3.0-P4.45,C720477,2
43,"FPC2, FPC3, FPC4",FPC-05F-6PH20,FPC-SMD_6P-P0.50_XUNPU_FPC-05F-6PH20,C2856796,3
44,4PINFAN1,N/A,4PIN_FAN_PWM,,1
45,FLASH1,N/A,FLASH,,1
46,FPC1,FPC-0.5FX-24PWBH20,FPC-SMD_XUNPU-FPC-0.5FX-24PWBH20,C3446015,1
47,LED1,"HL-PST-1608H233W(8000-12000K)",LED-SMD_L1.6-W0.8-RD-WHITE-2,C219228,1
48,POWER1,N/A,POWER,,1
49,Q1,SI1308EDL-T1-BE3,SOT-323_L2.0-W1.3-P1.30-LS2.1-BR,C3289597,1

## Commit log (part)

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2026-03-30 Update README with project details and usage instructions
    Added project overview, usage instructions, and motivation for building the air quality monitor.
2026-03-31 Create a
2026-03-31 Update README with changelog and formatting fixes
    Added a changelog and updated the formatting of the README.
2026-04-01 Add Bill of Materials section to README
    Added a Bill of Materials (BOM) section to the README with detailed component specifications.
2026-04-01 Modify AIO-AIR_BOM.csv with corrections and additions
    Updated part values and added links for components.
2026-04-02 Update README.md
    Added features section and improved monitoring details.
2026-04-02 Update README.md
    Added disclaimers regarding project use, liability, and regulatory compliance. Expanded project overview and usage instructions.
2026-05-15 Clarify flashing instructions in README
    Updated flashing instructions for clarity and added details about using USB flashing devices.
2026-05-20 Rename AIO-AIR_BOM.csv to bom.csv
2026-05-23 Update README with BOM details and images
    Added BOM table with detailed components and pricing.
2026-05-23 Rename bom (2).csv to bom.csv
2026-06-02 Fix formatting and enhance README content
    Correct formatting and improve clarity in the README regarding integration and features.
